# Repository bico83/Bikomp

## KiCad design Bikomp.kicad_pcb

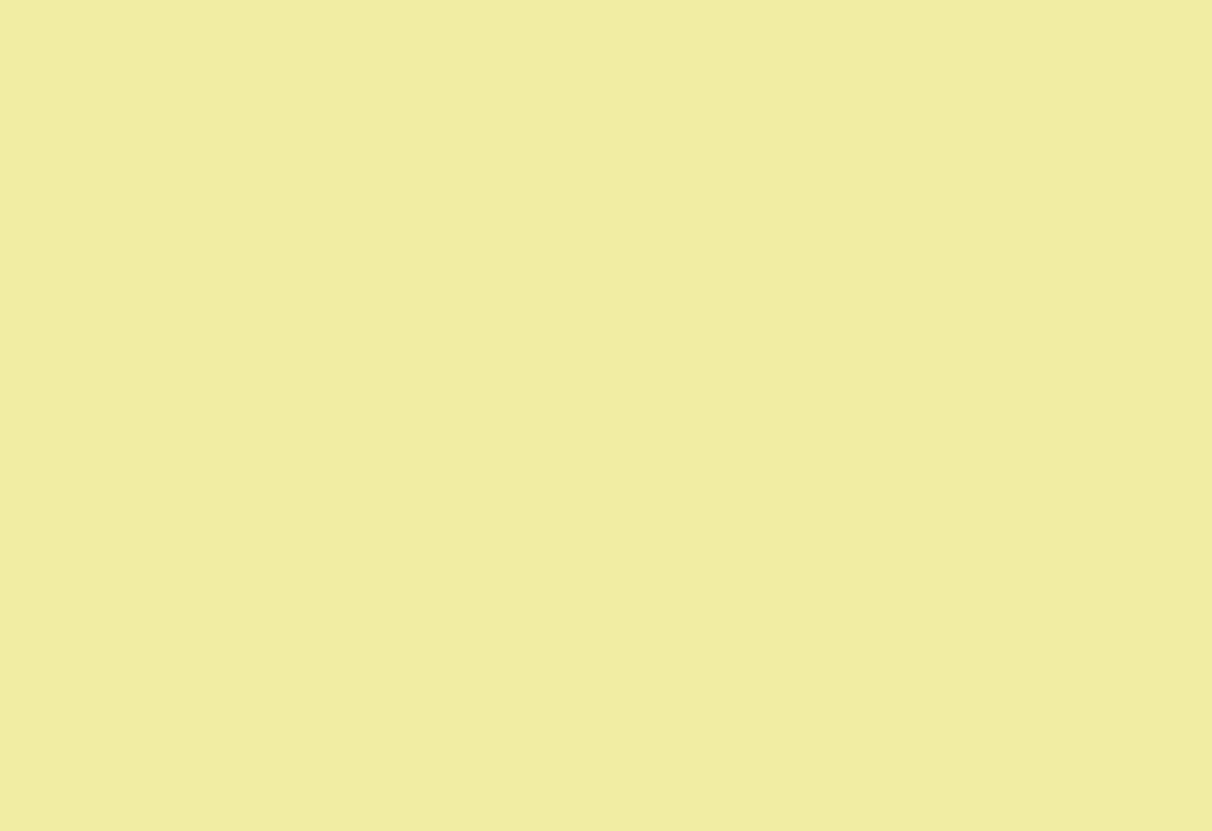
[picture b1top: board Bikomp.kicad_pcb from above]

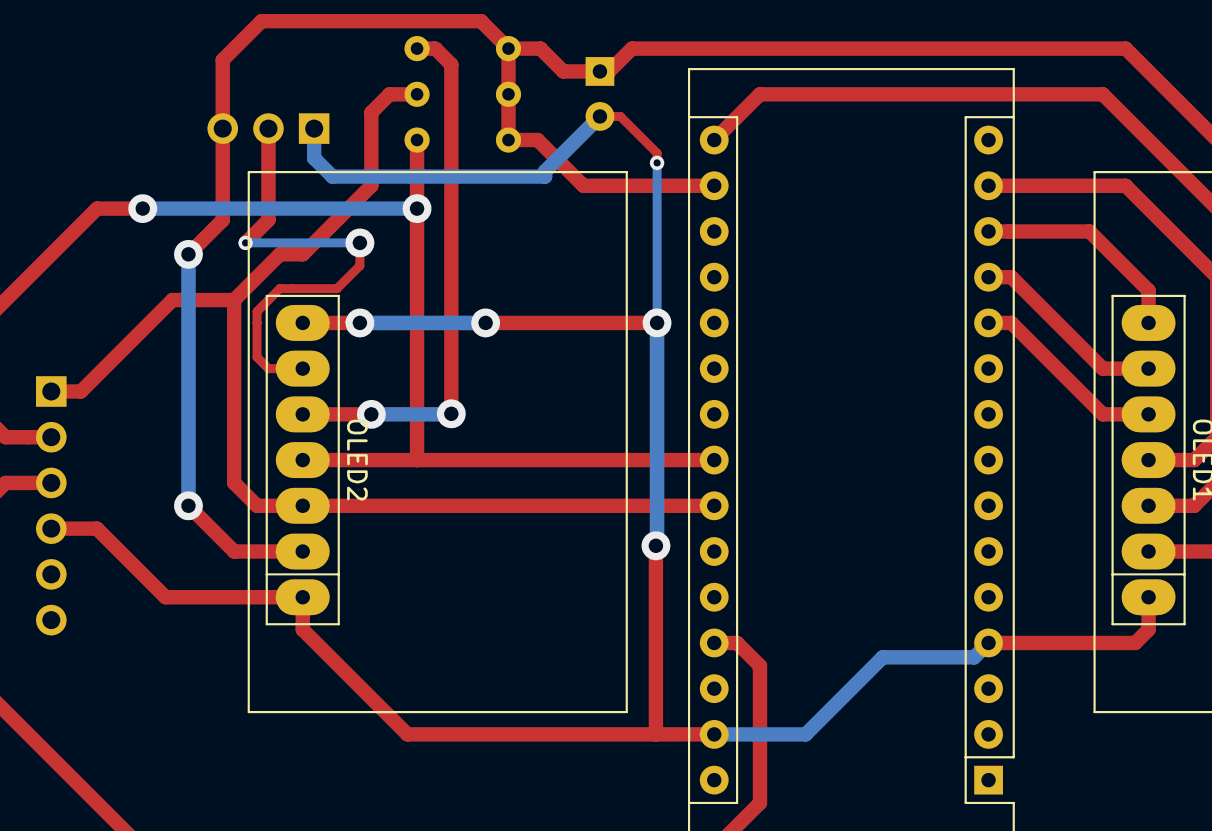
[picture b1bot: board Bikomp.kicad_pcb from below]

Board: 2 copper layers, 9 parts (3 on the bottom side), 12 nets.

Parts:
A1: Arduino_Nano_v3.x; Arduino_Nano
C1: 2.2uF; CP_Radial_D5.0mm_P2.50mm
J1: Conn_01x04_Female; PinHeader_1x06_P2.54mm_Vertical
OLED1, OLED2: SSD1306_7pin; SIP-7
R1, R2, R3: 10k; R_Axial_DIN0204_L3.6mm_D1.6mm_P5.08mm_Horizontal
SW1: SW_DPDT_x2; PinHeader_1x03_P2.54mm_Vertical

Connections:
+3V3: A1.17, C1.1, OLED1.2, OLED2.2, R1.1, R2.1, R3.1, SW1.3
+5V: A1.27, J1.3
D8: A1.11, OLED1.5
D9: A1.12, OLED1.6
D10: A1.13, OLED1.7
D11: A1.14, OLED1.4
D13: A1.16, OLED1.3
GND: A1.4, A1.29, C1.2, J1.4, OLED1.1, OLED2.1, OLED2.7, SW1.1
unnamed: OLED2.5, R3.2
unnamed: OLED2.6, SW1.2
SCL: A1.24, J1.1, OLED2.3, R2.2
SDA: A1.23, J1.2, OLED2.4, R1.2

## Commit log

2020-06-29 SW initial version
2020-06-29 Hardware related files.
    Two variants in PCB and schematic, regular and lowline, Bikomp.lib and SIP-7.kicad_mod contain the shared libraries
